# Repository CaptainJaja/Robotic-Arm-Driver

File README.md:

# Contrôleur "Rail-Bras-Ventouses" (STM32G4 + TMC2226)

Ce PCB est la carte de contrôle centrale du sous-système de préhension du robot. Elle orchestre les mouvements du rail, du bras et la gestion des ventouses.
Elle intègre une architecture de puissance à plusieurs étages pour gérer différents niveaux de tension (24V, 12V, 7.4V, 3.3V) à partir d'une batterie 6S, tout en pilotant une grande variété d'actionneurs via un **STM32G431**.

## ⚡ Architecture d'Alimentation (Power Tree)

L'alimentation est distribuée en cascade pour optimiser le rendement et la stabilité :

1.  **Entrée Principale :** Batterie LiPo 6S (~22.2V - 25.2V).
2.  **Étage 1 (V_BAT ➔ 12V) :** Buck **TI LM25145**.
    * *Usage :* Alimentation des Dynamixels et source pour les étages suivants.
3.  **Étage 2A (12V ➔ 7.4V) :** Buck **TI TPS563300**.
    * *Usage :* Alimentation de puissance pour les Servomoteurs classiques et les 4 moteurs DC (MCC).
4.  **Étage 2B (12V ➔ 3.3V) :** Module de puissance **Würth Elektronik MagI³C (173010x78)**.
    * *Usage :* Alimentation propre pour la logique (STM32, Capteurs).

## 🧠 Cœur Logique : STM32G431CBU6

* **MCU :** ARM Cortex-M4 à 170 MHz (Série G4 optimisée pour le contrôle moteur/mixte).
* **Programmation :** Connecteur **ST-Link** dédié (SWD).
* **Interface Utilisateur :**
    * 1x LED Power (3.3V).
    * 2x LEDs d'état (pilotables par GPIO).
    * 1x Bouton Reset.
    * 1x Bouton User (connecté sur GPIO/EXTI).

## 🦾 Contrôle Actionneurs

### 1. Axe "Rail" (Stepper) - TMC2226-SA
* **Driver :** Trinamic TMC2226 (Ultra-Silent).
* **Tension :** 24V (V_BAT).
* **Configuration :**
    * **Rsense :** 390 mΩ (Définit la plage de courant : Irms=0.56A).
    * **Microstepping :** Configurable via **DIP Switch** embarqué.
    * **Interface :** STEP / DIR + UART (Diag).
* **❄️ Gestion Thermique Avancée :**
    * Le Pad thermique du TMC2226 est soudé sur un large plan de cuivre.
    * Réseau de **vias thermiques** traversant le PCB vers une zone de cuivre exposée sur la face opposée.
    * Emplacement prévu pour coller une ailette de refroidissement (heatsink) directement sur la zone arrière.

### 2. Bras & Ventouses
* **2x Servomoteurs :** Alimentés en 7.4V (PWM direct).
* **2x Dynamixels :** Connecteurs dédiés (GND, 12V, Data).
    * *Protocole :* UART Half-Duplex (compatible protocole Robotis).
* **4x Moteurs DC (MCC) :** Sorties alimentées en 7.4V (pour pompes à vide/ventouses).

## 🔌 Connectivité & Capteurs

* **Capteur ToF (Time of Flight) :** Connecteur dédié (I2C + GPIOs + 3.3V).
* **Expansions :** 3 rangées de headers [GND - 3V3 - GPIO] pour ajouts futurs.

## 🐛 Debug & Instrumentation

Le PCB intègre des points de test (headers) regroupés pour faciliter l'analyse à l'oscilloscope ou à l'analyseur logique :

* `PWM_Servo1`, `PWM_Servo2`
* `UART_Dynamixel1`, `UART_Dynamixel2`
* `STEP`, `PDN`, `INDEX`, `DIAG` (Signaux du TMC2226)

## 🛠️ Vues du PCB

| Face Composants | Face Cuivre |
| :---: | :---: |
|  |  |

---
## License

This hardware project is licensed under the **CERN Open Hardware Licence Version 2 - Strongly Reciprocal (CERN-OHL-S v2)**.

You may redistribute and modify this documentation and make products using it under the terms of the CERN-OHL-S v2. If you modify or distribute this design, you must share your modifications and the entire product it is integrated into under the same open-source license.

Designed by C. Janus.

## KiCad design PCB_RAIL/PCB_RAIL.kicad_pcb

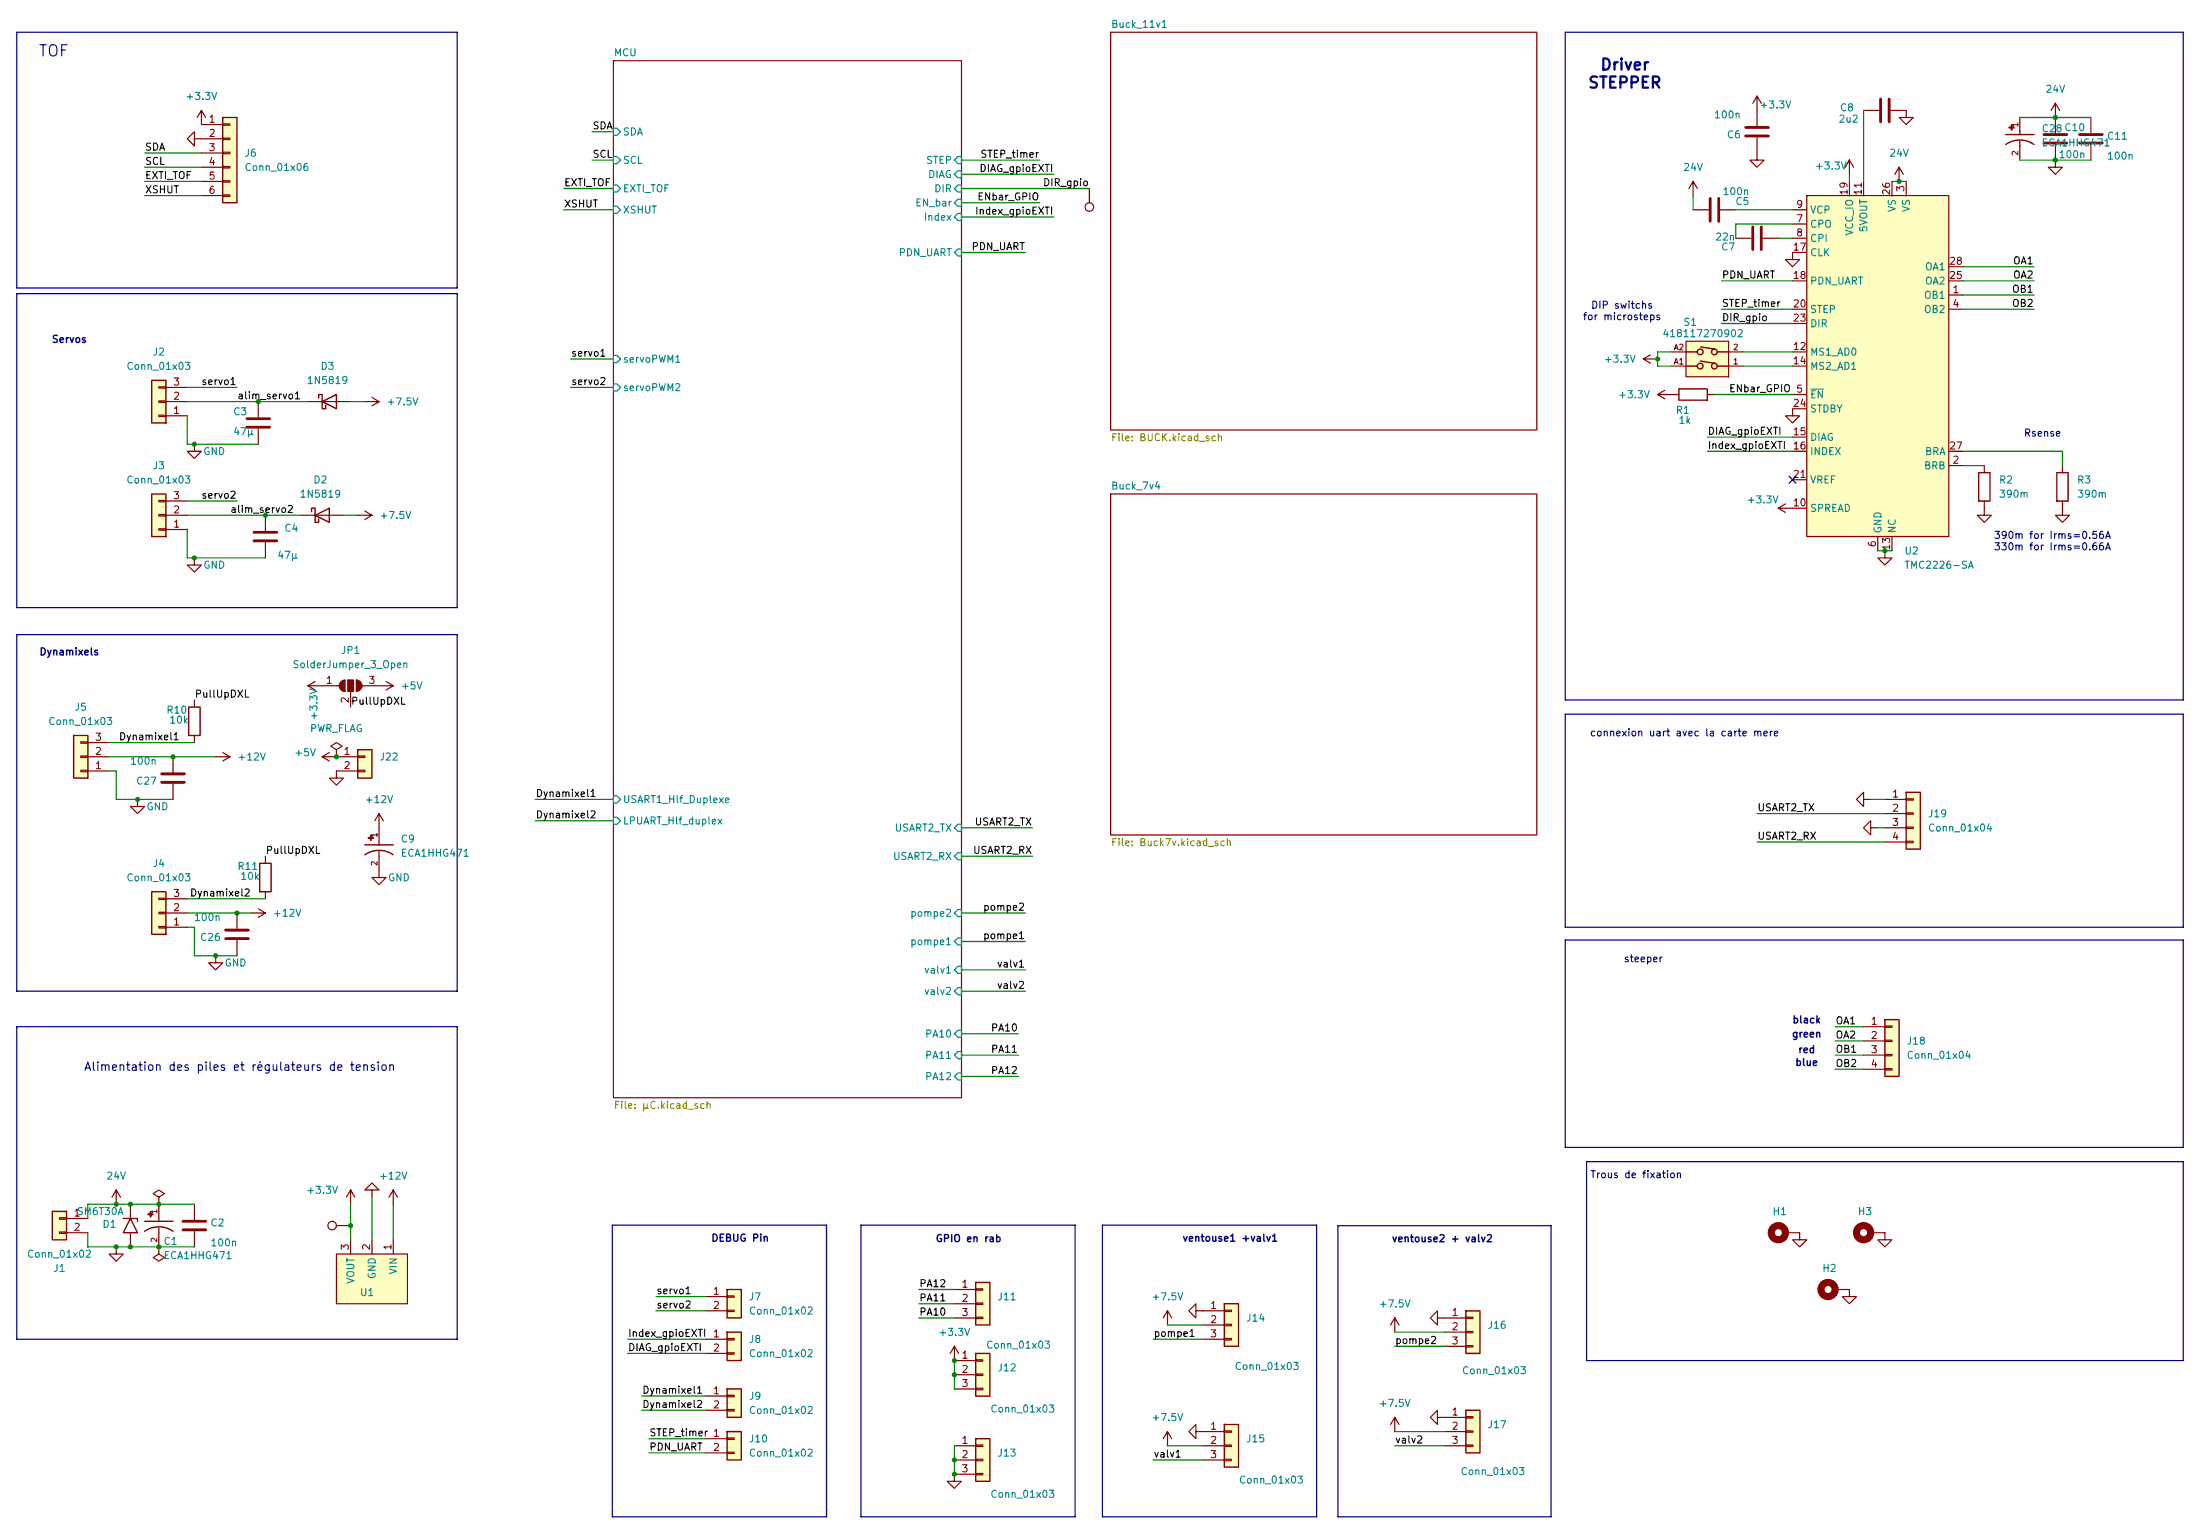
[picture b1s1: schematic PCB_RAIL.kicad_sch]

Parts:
C1, C9, C28: ECA1HHG471; PARTREV 20-DEC-19
C2, C5, C10, C11: 100n; C_0603_1608Metric
C3, C4: 47µ; C_1210_3225Metric
C6, C26, C27: 100n; C_0402_1005Metric
C7: 22n; C_0603_1608Metric
C8: 2u2; C_0603_1608Metric
D1: SM6T30A; D_SMB
D2, D3: 1N5819; D_SOD-123
H1, H2, H3: MountingHole_Pad; MountingHole_2.2mm_M2_Pad_Via
J1: Conn_01x02; XT30-F-2P
J2, J3, J14, J15, J16, J17: Conn_01x03; JST_EH_B3B-EH-A_1x03_P2.50mm_Vertical
J4, J5: Conn_01x03; JST_PH_B3B-PH-K_1x03_P2.00mm_Vertical
J6: Conn_01x06; JST_EH_B6B-EH-A_1x06_P2.50mm_Vertical
J7, J8, J9, J10: Conn_01x02; PinHeader_1x02_P2.54mm_Vertical
J11, J12, J13: Conn_01x03; PinHeader_1x03_P2.54mm_Vertical
J18, J19: Conn_01x04; JST_EH_B4B-EH-A_1x04_P2.50mm_Vertical
J22: Conn_01x02; JST_PH_B2B-PH-K_1x02_P2.00mm_Vertical
JP1: SolderJumper_3_Open; SolderJumper-3_P1.3mm_Open_Pad1.0x1.5mm
R1: 1k; R_0402_1005Metric
R2, R3: 390m; 561070332071
R10, R11: 10k; R_0402_1005Metric
S1: 418117270902
TP1, TP2: TestPoint; TestPoint_Pad_D1.0mm
U1: WPME-FDSM_17301XX35; MPN 173010x78
U2: TMC2226-SA; TMC2226

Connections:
24V: C1.1, C2.1, C5.1, C10.1, C11.1, C28.1, D1.1 (A1), J1.1, U2.3 (VS), U2.26 (VS); also elsewhere on the board
+3.3V: C6.2, J6.1, J12.1, J12.2, J12.3, JP1.1 (A), R1.1, S1.A1, S1.A2, TP1.1, U1.3 (VOUT), U2.10 (SPREAD), U2.19 (VCC_IO); also elsewhere on the board
+5V: J22.1, JP1.3 (B)
+7.5V: D2.2 (A), D3.2 (A), J14.2, J15.2, J16.2, J17.2; also elsewhere on the board
+12V: C9.1, C26.2, C27.2, J4.2, J5.2, U1.1 (VIN); also elsewhere on the board
/DIAG_gpioEXTI: J8.2, U2.15 (DIAG); also elsewhere on the board
/DIR_gpio: TP2.1, U2.23 (DIR); also elsewhere on the board
/Dynamixel1: J5.3, J9.1, R10.2; also elsewhere on the board
/Dynamixel2: J4.3, J9.2, R11.2; also elsewhere on the board
/ENbar_GPIO: R1.2, U2.5 (~EN); also elsewhere on the board
/EXTI_TOF: J6.5; also elsewhere on the board
/Index_gpioEXTI: J8.1, U2.16 (INDEX); also elsewhere on the board
/OA1: J18.1, U2.28 (OA1)
/OA2: J18.2, U2.25 (OA2)
/OB1: J18.3, U2.1 (OB1)
/OB2: J18.4, U2.4 (OB2)
/PA10: J11.3; also elsewhere on the board
/PA11: J11.2; also elsewhere on the board
/PA12: J11.1; also elsewhere on the board
/PDN_UART: J10.2, U2.18 (PDN_UART); also elsewhere on the board
/PullUpDXL: JP1.2 (C), R10.1, R11.1
/SCL: J6.4; also elsewhere on the board
/SDA: J6.3; also elsewhere on the board
/STEP_timer: J10.1, U2.20 (STEP); also elsewhere on the board
/USART2_RX: J19.4; also elsewhere on the board
/USART2_TX: J19.2; also elsewhere on the board
/XSHUT: J6.6; also elsewhere on the board
/alim_servo1: C3.1, D3.1 (K), J2.2
/alim_servo2: C4.1, D2.1 (K), J3.2
/pompe1: J14.3; also elsewhere on the board
/pompe2: J16.3; also elsewhere on the board
/servo1: J2.3, J7.1; also elsewhere on the board
/servo2: J3.3, J7.2; also elsewhere on the board
/valv1: J15.3; also elsewhere on the board
/valv2: J17.3; also elsewhere on the board
GND: C1.2, C2.2, C3.2, C4.2, C6.1, C8.1, C9.2, C10.2, C11.2, C26.1, C27.1, C28.2, D1.2 (A2), H1.1, H2.1, H3.1, J1.2, J2.1, J3.1, J4.1, J5.1, J6.2, J13.1, J13.2, J13.3, J14.1, J15.1, J16.1, J17.1, J19.1, J19.3, J22.2, R2.2, R3.2, U1.2 (GND), U2.6 (GND), U2.13 (NC), U2.17 (CLK), U2.22 (GND), U2.24 (STDBY), U2.29 (GND); also elsewhere on the board
unnamed: C8.2, U2.11 (5VOUT)
unnamed: R3.1, U2.27 (BRA)
unnamed: R2.1, U2.2 (BRB)
unnamed: C7.2, U2.8 (CPI)
unnamed: C7.1, U2.7 (CPO)
unnamed: S1.2, U2.12 (MS1_AD0)
unnamed: S1.1, U2.14 (MS2_AD1)
unnamed: C5.2, U2.9 (VCP)

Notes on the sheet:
DEBUG Pin
green
Trous de fixation
ventouse2 + valv2
Alimentation des piles et régulateurs de tension
Driver STEPPER
Servos
connexion uart avec la carte mere
red
Dynamixels
Rsense
TOF
ventouse1 +valv1
blue
390m for Irms=0.56A 330m for Irms=0.66A
steeper
DIP switchs for microsteps
black
GPIO en rab

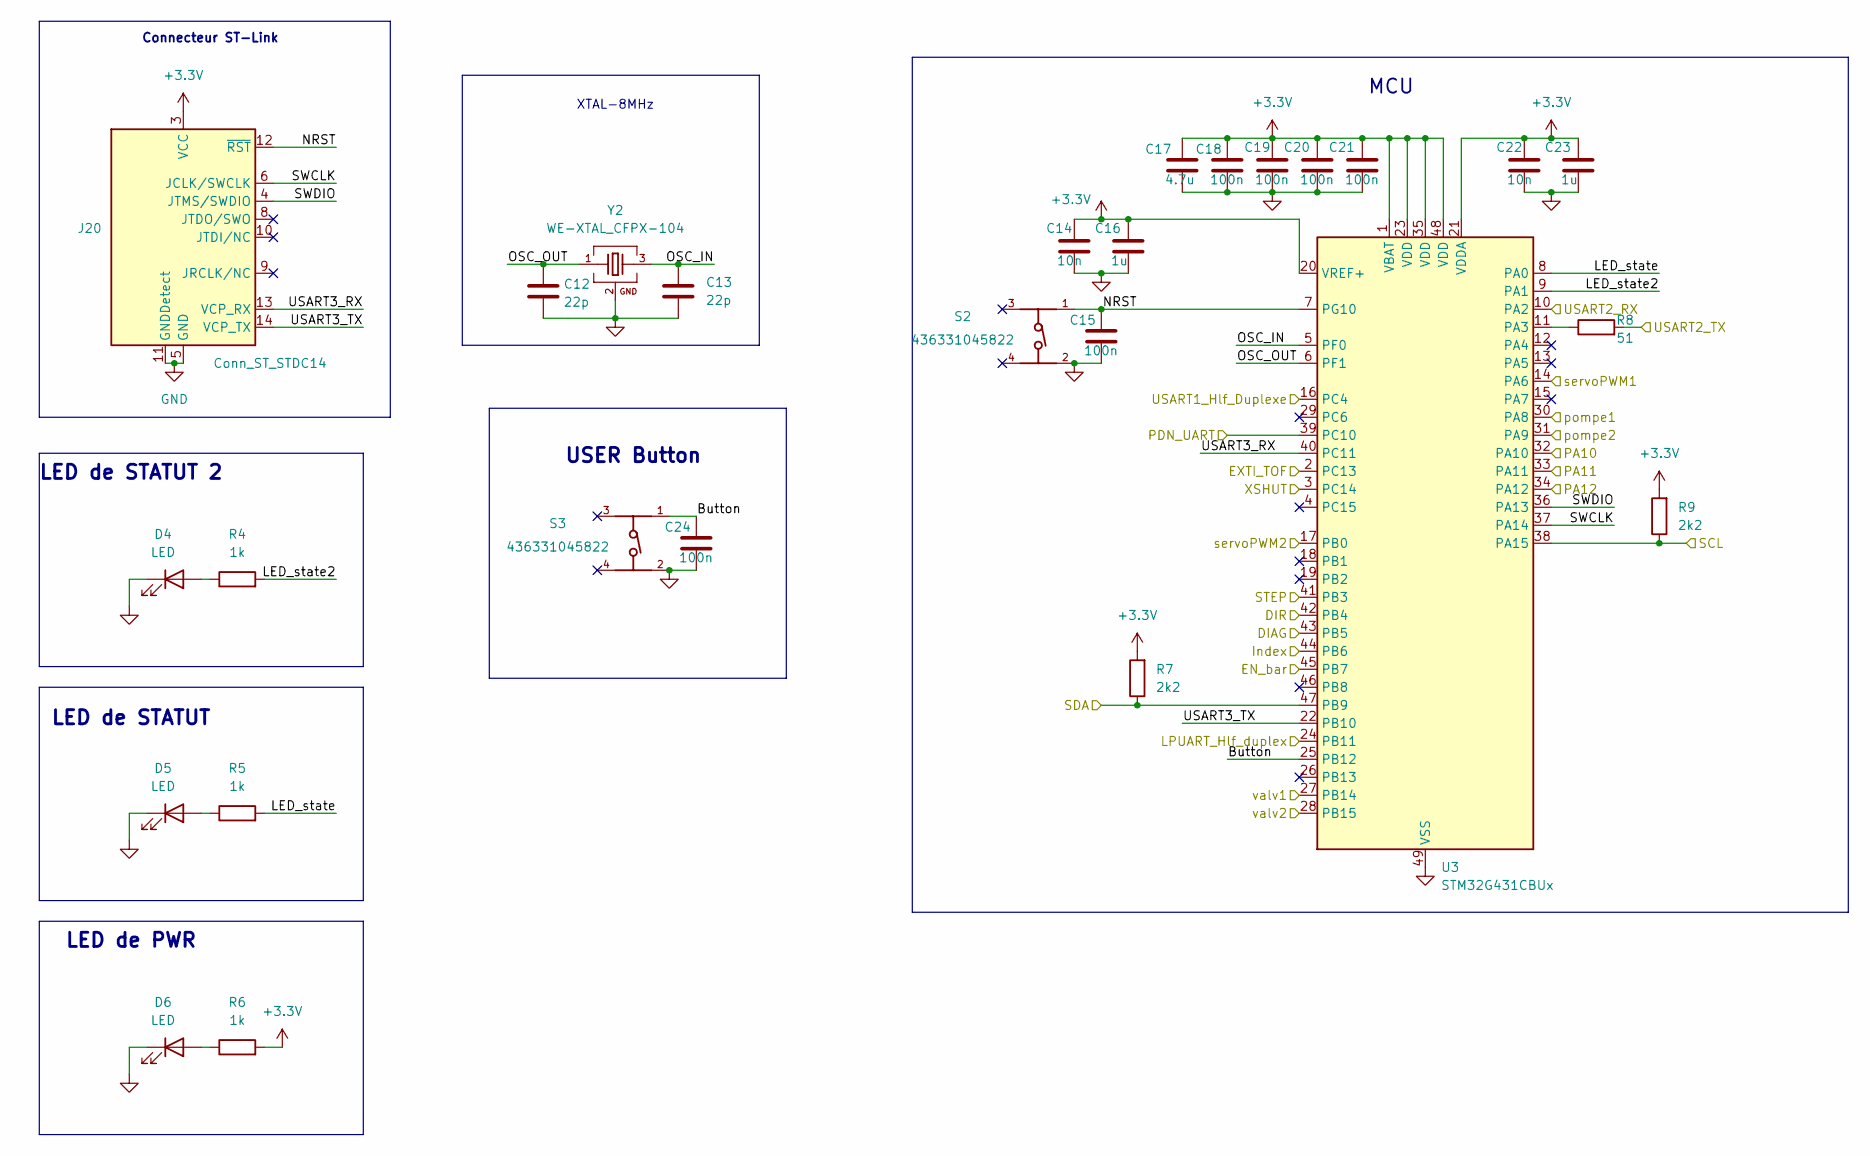
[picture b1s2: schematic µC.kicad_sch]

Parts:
C12, C13: 22p; C_0603_1608Metric
C14, C22: 10n; C_0402_1005Metric
C15, C18, C19, C20, C21, C24: 100n; C_0402_1005Metric
C16, C23: 1u; C_0402_1005Metric
C17: 4.7u; C_0402_1005Metric
D4, D5, D6: LED; LED_0603_1608Metric_Pad1.05x0.95mm_HandSolder
J20: Conn_ST_STDC14; PinHeader_2x07_P1.27mm_Vertical_SMD
R4, R5, R6: 1k; R_0402_1005Metric
R7, R9: 2k2; R_0402_1005Metric
R8: 51; R_0402_1005Metric
S2, S3: 436331045822
U3: STM32G431CBUx; STM32G431CBU6
Y2: WE-XTAL_CFPX-104; DigiKey_Part_Number 1923-830055663CT-ND

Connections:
+3.3V: C14.1, C16.1, C17.1, C18.1, C19.1, C20.1, C21.1, C22.1, C23.1, J20.3 (VCC), R6.2, R7.2, R9.2, U3.1 (VBAT), U3.20 (VREF+), U3.21 (VDDA), U3.23 (VDD), U3.35 (VDD), U3.48 (VDD); also elsewhere on the board
/DIAG_gpioEXTI: U3.43 (PB5); also elsewhere on the board
/DIR_gpio: U3.42 (PB4); also elsewhere on the board
/Dynamixel1: U3.16 (PC4); also elsewhere on the board
/Dynamixel2: U3.24 (PB11); also elsewhere on the board
/ENbar_GPIO: U3.45 (PB7); also elsewhere on the board
/EXTI_TOF: U3.2 (PC13); also elsewhere on the board
/Index_gpioEXTI: U3.44 (PB6); also elsewhere on the board
/MCU/Button: C24.1, S3.1, U3.25 (PB12)
/MCU/LED_state: R5.2, U3.8 (PA0)
/MCU/LED_state2: R4.2, U3.9 (PA1)
/MCU/NRST: C15.1, J20.12 (~RST), S2.1, U3.7 (PG10)
/MCU/OSC_IN: C13.1, U3.5 (PF0), Y2.3
/MCU/OSC_OUT: C12.1, U3.6 (PF1), Y2.1
/MCU/SWCLK: J20.6 (JCLK/SWCLK), U3.37 (PA14)
/MCU/SWDIO: J20.4 (JTMS/SWDIO), U3.36 (PA13)
/MCU/USART3_RX: J20.13 (VCP_RX), U3.40 (PC11)
/MCU/USART3_TX: J20.14 (VCP_TX), U3.22 (PB10)
/PA10: U3.32 (PA10); also elsewhere on the board
/PA11: U3.33 (PA11); also elsewhere on the board
/PA12: U3.34 (PA12); also elsewhere on the board
/PDN_UART: U3.39 (PC10); also elsewhere on the board
/SCL: R9.1, U3.38 (PA15); also elsewhere on the board
/SDA: R7.1, U3.47 (PB9); also elsewhere on the board
/STEP_timer: U3.41 (PB3); also elsewhere on the board
/USART2_RX: U3.10 (PA2); also elsewhere on the board
/USART2_TX: R8.2; also elsewhere on the board
/XSHUT: U3.3 (PC14); also elsewhere on the board
/pompe1: U3.30 (PA8); also elsewhere on the board
/pompe2: U3.31 (PA9); also elsewhere on the board
/servo1: U3.14 (PA6); also elsewhere on the board
/servo2: U3.17 (PB0); also elsewhere on the board
/valv1: U3.27 (PB14); also elsewhere on the board
/valv2: U3.28 (PB15); also elsewhere on the board
GND: C12.2, C13.2, C14.2, C15.2, C16.2, C17.2, C18.2, C19.2, C20.2, C21.2, C22.2, C23.2, C24.2, D4.1 (K), D5.1 (K), D6.1 (K), J20.5 (GND), J20.7 (GND), J20.11 (GNDDetect), S2.2, S3.2, U3.49 (VSS), Y2.2, Y2.4; also elsewhere on the board
unnamed: D4.2 (A), R4.1
unnamed: D5.2 (A), R5.1
unnamed: D6.2 (A), R6.1
unnamed: R8.1, U3.11 (PA3)

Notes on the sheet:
LED de STATUT 2
LED de STATUT
XTAL-8MHz
LED de PWR
Connecteur ST-Link
USER Button
MCU

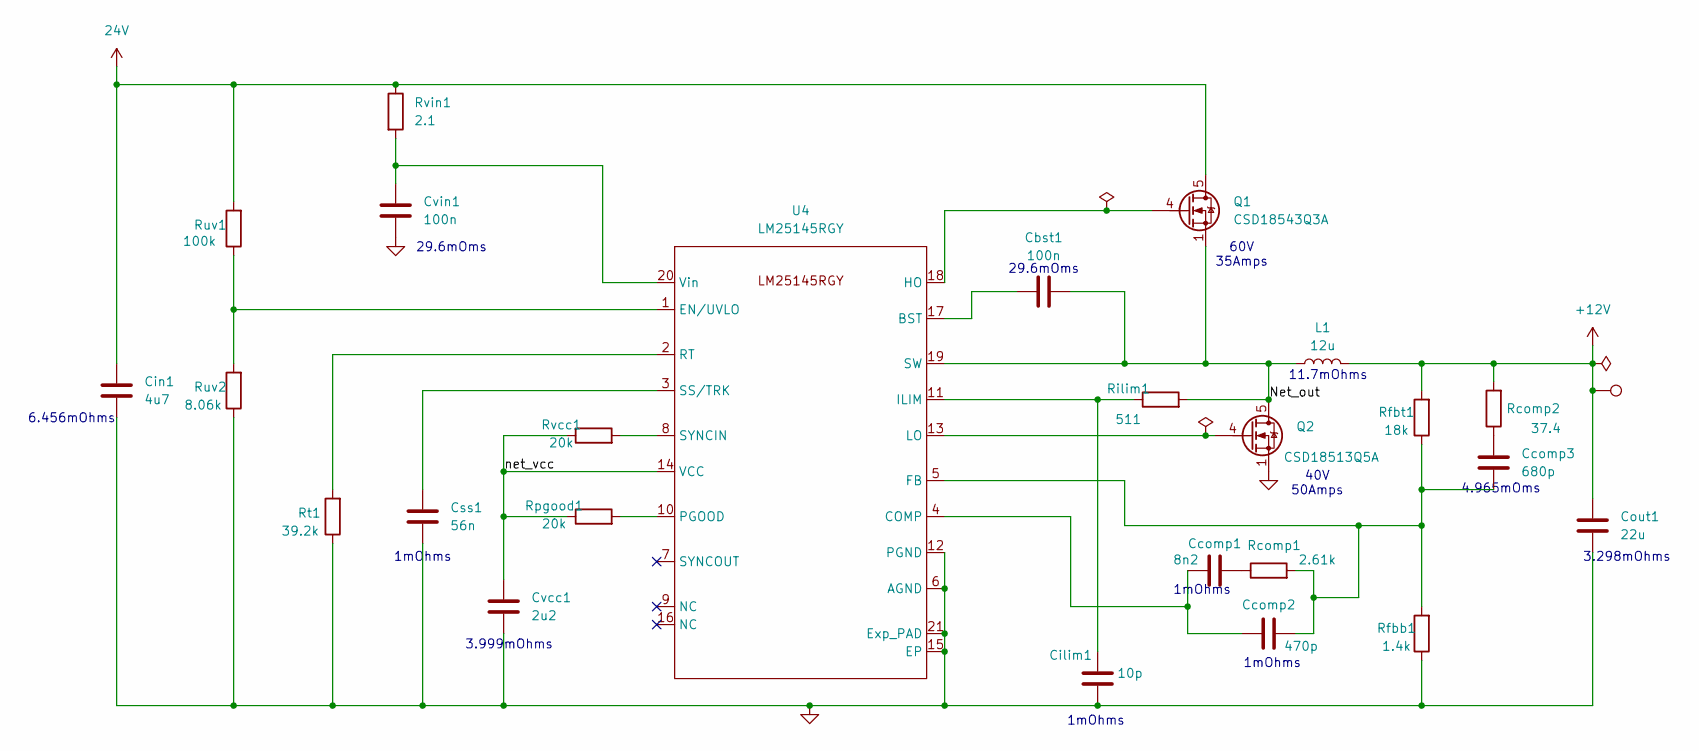
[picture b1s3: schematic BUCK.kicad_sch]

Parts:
Cbst1: 100n; C_0603_1608Metric
Ccomp1: 8n2; C_0402_1005Metric
Ccomp2: 470p; C_0402_1005Metric
Ccomp3: 680p; C_0402_1005Metric
Cilim1: 10p; C_0603_1608Metric
Cin1: 4u7; C_1210_3225Metric
Cout1: 22u; C_1210_3225Metric
Css1: 56n; C_0402_1005Metric
Cvcc1: 2u2; C_1206_3216Metric
Cvin1: 100n; C_0603_1608Metric
L1: 12u; L_12x12mm_H8mm
Q1: CSD18543Q3A; TRANS_CSD18543Q3A
Q2: CSD18513Q5A; TRANS_CSD18534Q5A
Rcomp1: 2.61k; R_0402_1005Metric
Rcomp2: 37.4; R_0402_1005Metric
Rfbb1: 1.4k; R_0402_1005Metric
Rfbt1: 18k; R_0603_1608Metric
Rilim1: 511; R_0402_1005Metric
Rpgood1: 20k; R_0603_1608Metric
Rt1: 39.2k; R_0402_1005Metric
Ruv1: 100k; R_0402_1005Metric
Ruv2: 8.06k; R_0603_1608Metric
Rvcc1: 20k; L_0603_1608Metric
Rvin1: 2.1; R_0603_1608Metric
TP3: TestPoint; TestPoint_Pad_D1.0mm
U4: LM25145RGY; IC_LM25145RGYR

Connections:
24V: Cin1.1, Q1.5 (D), Ruv1.2, Rvin1.1; also elsewhere on the board
+12V: Cout1.2, L1.2, Rcomp2.2, Rfbt1.2, TP3.1; also elsewhere on the board
/Buck_11v1/Net_out: Cbst1.2, L1.1, Q1.1 (S), Q1.2 (S), Q1.3 (S), Q2.5 (D), Rilim1.2, U4.19 (SW)
/Buck_11v1/net_vcc: Cvcc1.1, Rpgood1.1, Rvcc1.1, U4.14 (VCC)
GND: Cilim1.2, Cin1.2, Cout1.1, Css1.2, Cvcc1.2, Cvin1.2, Q2.1 (S), Q2.2 (S), Q2.3 (S), Rfbb1.1, Rt1.1, Ruv2.1, U4.6 (AGND), U4.12 (PGND), U4.15 (EP), U4.21 (Exp_PAD); also elsewhere on the board
unnamed: Ccomp1.1, Rcomp1.1
unnamed: Ccomp3.2, Rcomp2.1
unnamed: Q1.4 (G), U4.18 (HO)
unnamed: Q2.4 (G), U4.13 (LO)
unnamed: Cbst1.1, U4.17 (BST)
unnamed: Ccomp1.2, Ccomp2.2, U4.4 (COMP)
unnamed: Ruv1.1, Ruv2.2, U4.1 (EN/UVLO)
unnamed: Ccomp2.1, Ccomp3.1, Rcomp1.2, Rfbb1.2, Rfbt1.1, U4.5 (FB)
unnamed: Cilim1.1, Rilim1.1, U4.11 (ILIM)
unnamed: Rpgood1.2, U4.10 (PGOOD)
unnamed: Rt1.2, U4.2 (RT)
unnamed: Css1.1, U4.3 (SS/TRK)
unnamed: Rvcc1.2, U4.8 (SYNCIN)
unnamed: Cvin1.1, Rvin1.2, U4.20 (Vin)

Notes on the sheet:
1mOhms
3.999mOhms
29.6mOms
60V 35Amps
40V 50Amps
11.7mOhms
3.298mOhms
1mOhms
4.965mOms
6.456mOhms

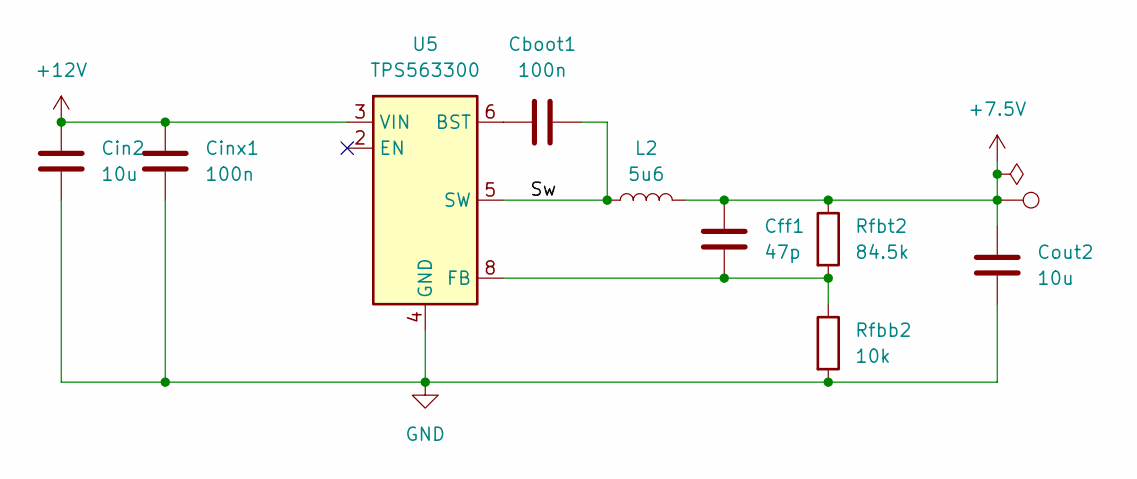
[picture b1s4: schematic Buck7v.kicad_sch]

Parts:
Cboot1: 100n; C_0402_1005Metric
Cff1: 47p; C_0402_1005Metric
Cin2: 10u; C_1206_3216Metric
Cinx1: 100n; C_0603_1608Metric
Cout2: 10u; C_0805_2012Metric
L2: 5u6; IND_ECS-MPIL0630-5R6MC
Rfbb2: 10k; R_0402_1005Metric
Rfbt2: 84.5k; R_0402_1005Metric
TP4: TestPoint; TestPoint_Pad_D1.0mm
U5: TPS563300; SOT-583-8

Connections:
+7.5V: Cff1.1, Cout2.1, L2.2, Rfbt2.1, TP4.1; also elsewhere on the board
+12V: Cin2.1, Cinx1.1, U5.3 (VIN); also elsewhere on the board
/Buck_7v4/Sw: Cboot1.2, L2.1, U5.5 (SW)
GND: Cin2.2, Cinx1.2, Cout2.2, Rfbb2.2, U5.4 (GND); also elsewhere on the board
unnamed: Cboot1.1, U5.6 (BST)
unnamed: Cff1.2, Rfbb2.1, Rfbt2.2, U5.8 (FB)

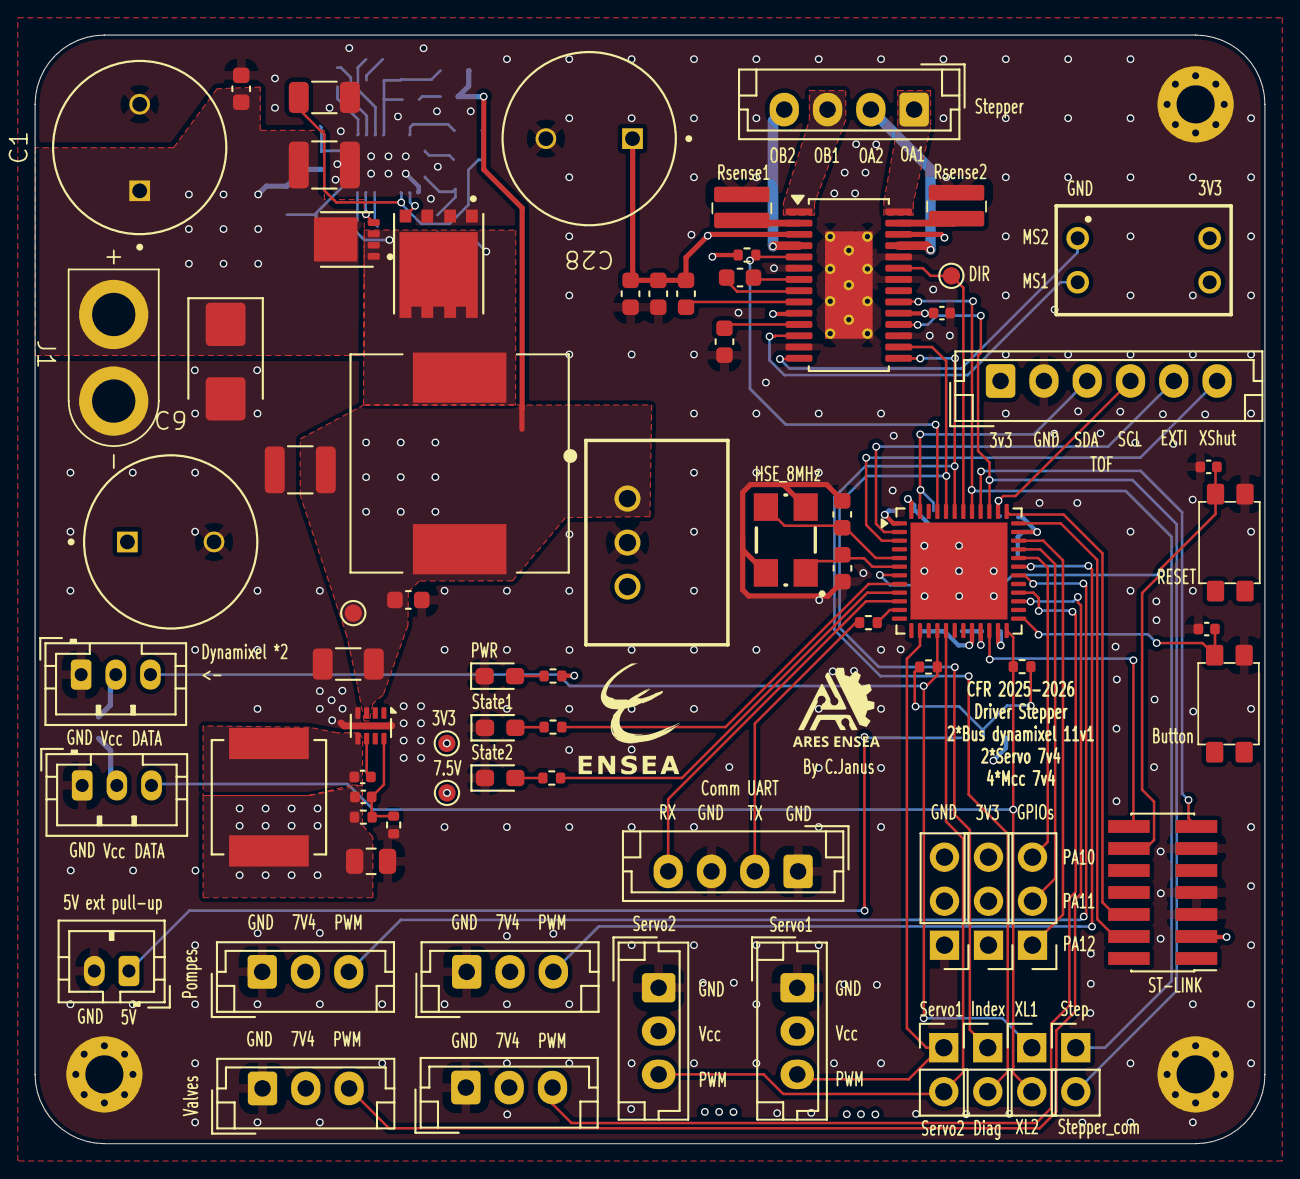
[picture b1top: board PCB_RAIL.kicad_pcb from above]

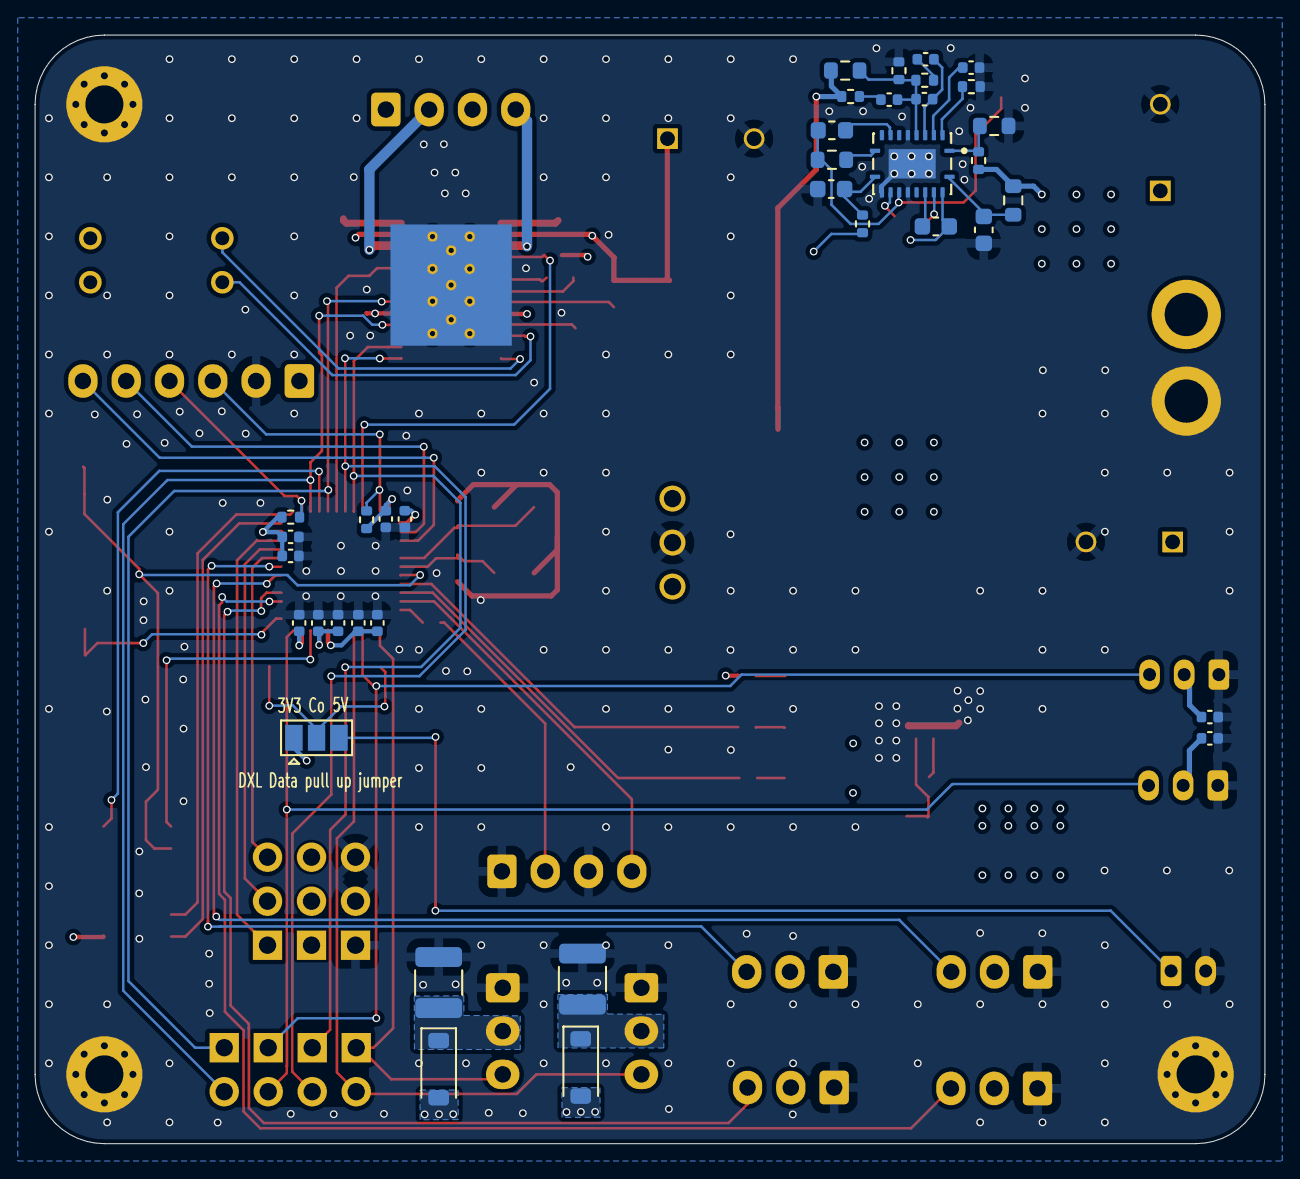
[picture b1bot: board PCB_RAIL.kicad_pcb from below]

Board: 4 copper layers, 71.0 x 64.0 mm, 114 parts (37 on the bottom side), 77 nets.

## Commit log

2026-05-17 Publication du projet sur github
2026-05-17 final push readme+3d
